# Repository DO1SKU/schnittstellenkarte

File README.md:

# schnittstellenkarte

Reichelt Bestellliste: https://www.reichelt.de/my/1758084

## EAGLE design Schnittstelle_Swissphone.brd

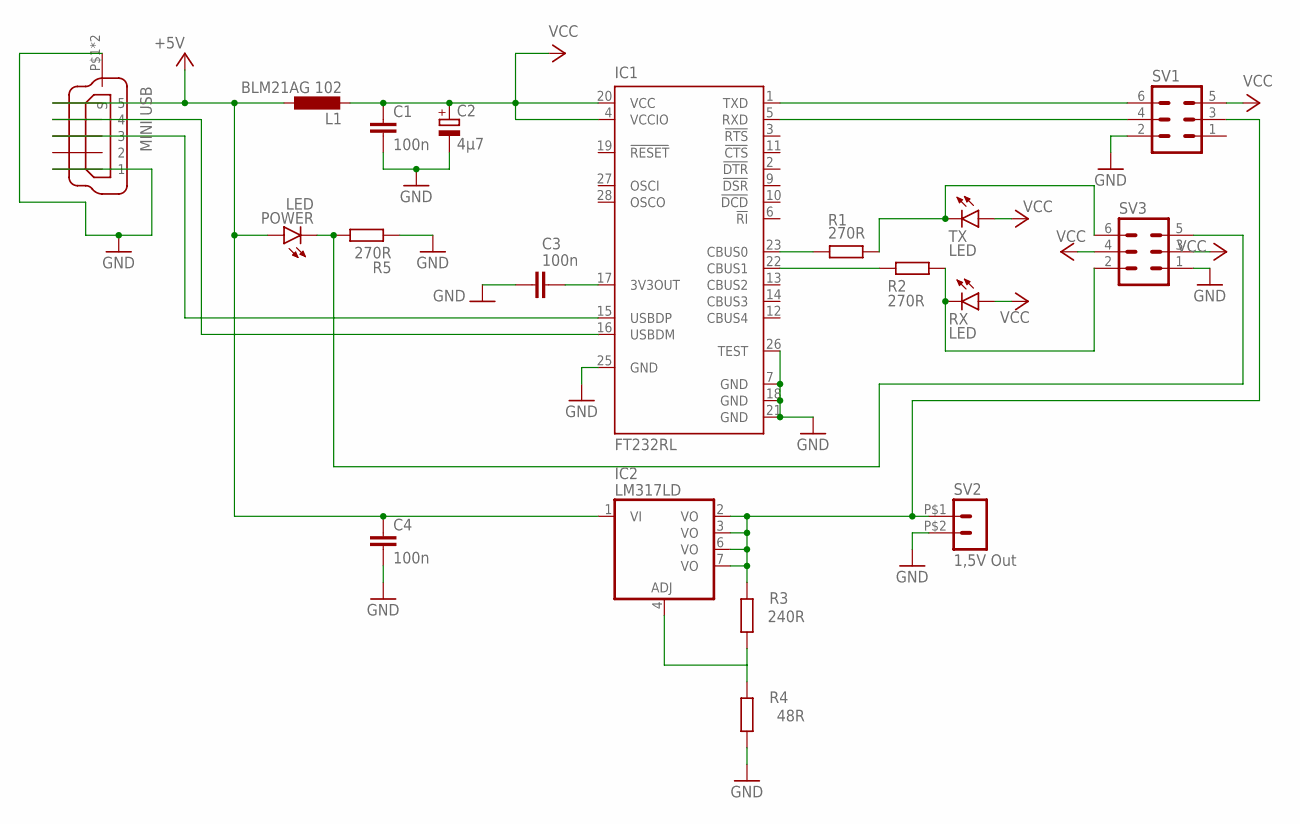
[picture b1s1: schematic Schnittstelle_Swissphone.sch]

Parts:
C1, C3, C4: 100n; C0603
C2: 4µ7; A/3216-18W
IC1: FT232RL; SSOP28
IC2: LM317LD; SO08
L1: BLM21AG 102; L2012C
POWER: LED; LED3MM
R1, R2, R5: 270R; R0603
R3: 240R; R1206
R4: 48R; R1206
RX: LED; LED3MM
SV1, SV3: ML6
SV2: 1,5V Out; 43650-0200
TX: LED; LED3MM
U$2: MINI USB; USBBWM

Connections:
+5V: C4.1, IC2.1 (VI), L1.1, POWER.A, U$2.P$3 (5)
GND: C1.2, C2.-, C3.2, C4.2, IC1.7 (GND), IC1.18 (GND), IC1.21 (GND), IC1.25 (GND), IC1.26 (TEST), R4.1, R5.1, SV1.2, SV2.P$2 (2), SV3.1, U$2.P$1 (S), U$2.P$2 (S), U$2.P$7 (1)
unnamed: IC1.23 (CBUS0), R1.1
unnamed: R2.2, RX.K (C), SV3.2
unnamed: R1.2, SV3.6, TX.K (C)
unnamed: IC1.5 (RXD), SV1.4
unnamed: IC2.2 (VO), IC2.3 (VO), IC2.6 (VO), IC2.7 (VO), R3.2, SV1.3, SV2.P$1 (1)
unnamed: IC2.4 (ADJ), R3.1, R4.2
unnamed: C3.1, IC1.17 (3V3OUT)
unnamed: POWER.K (C), R5.2, SV3.5
unnamed: IC1.16 (USBDM), U$2.P$4 (4)
unnamed: IC1.15 (USBDP), U$2.P$5 (3)
unnamed: IC1.22 (CBUS1), R2.1
unnamed: IC1.1 (TXD), SV1.6
VCC: C1.1, C2.+, IC1.4 (VCCIO), IC1.20 (VCC), L1.2, RX.A, SV1.5, SV3.3, SV3.4, TX.A

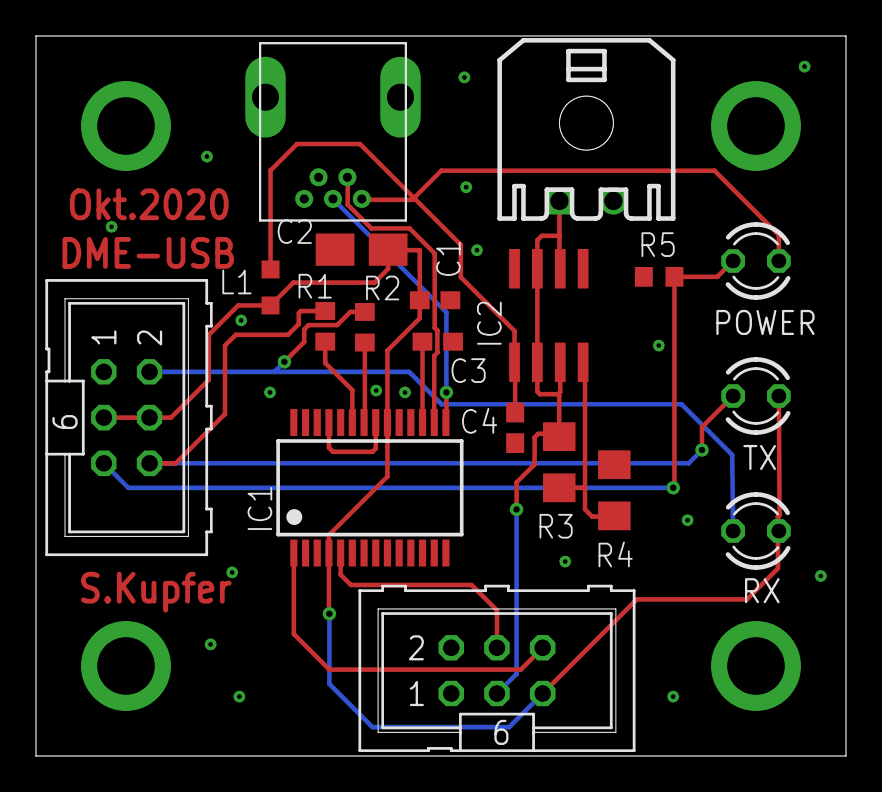
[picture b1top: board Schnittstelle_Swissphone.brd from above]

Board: 2 copper layers, 45.0 x 40.0 mm, 19 parts (0 on the bottom side), 15 nets.

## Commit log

2020-10-02 First Version
    With WEMOS D1
2020-10-02 add Arduino Nano and ENC28J60
2020-10-02 Add Layout
2020-10-02 PCB wo. Ethernet
2020-10-22 bug fixes
